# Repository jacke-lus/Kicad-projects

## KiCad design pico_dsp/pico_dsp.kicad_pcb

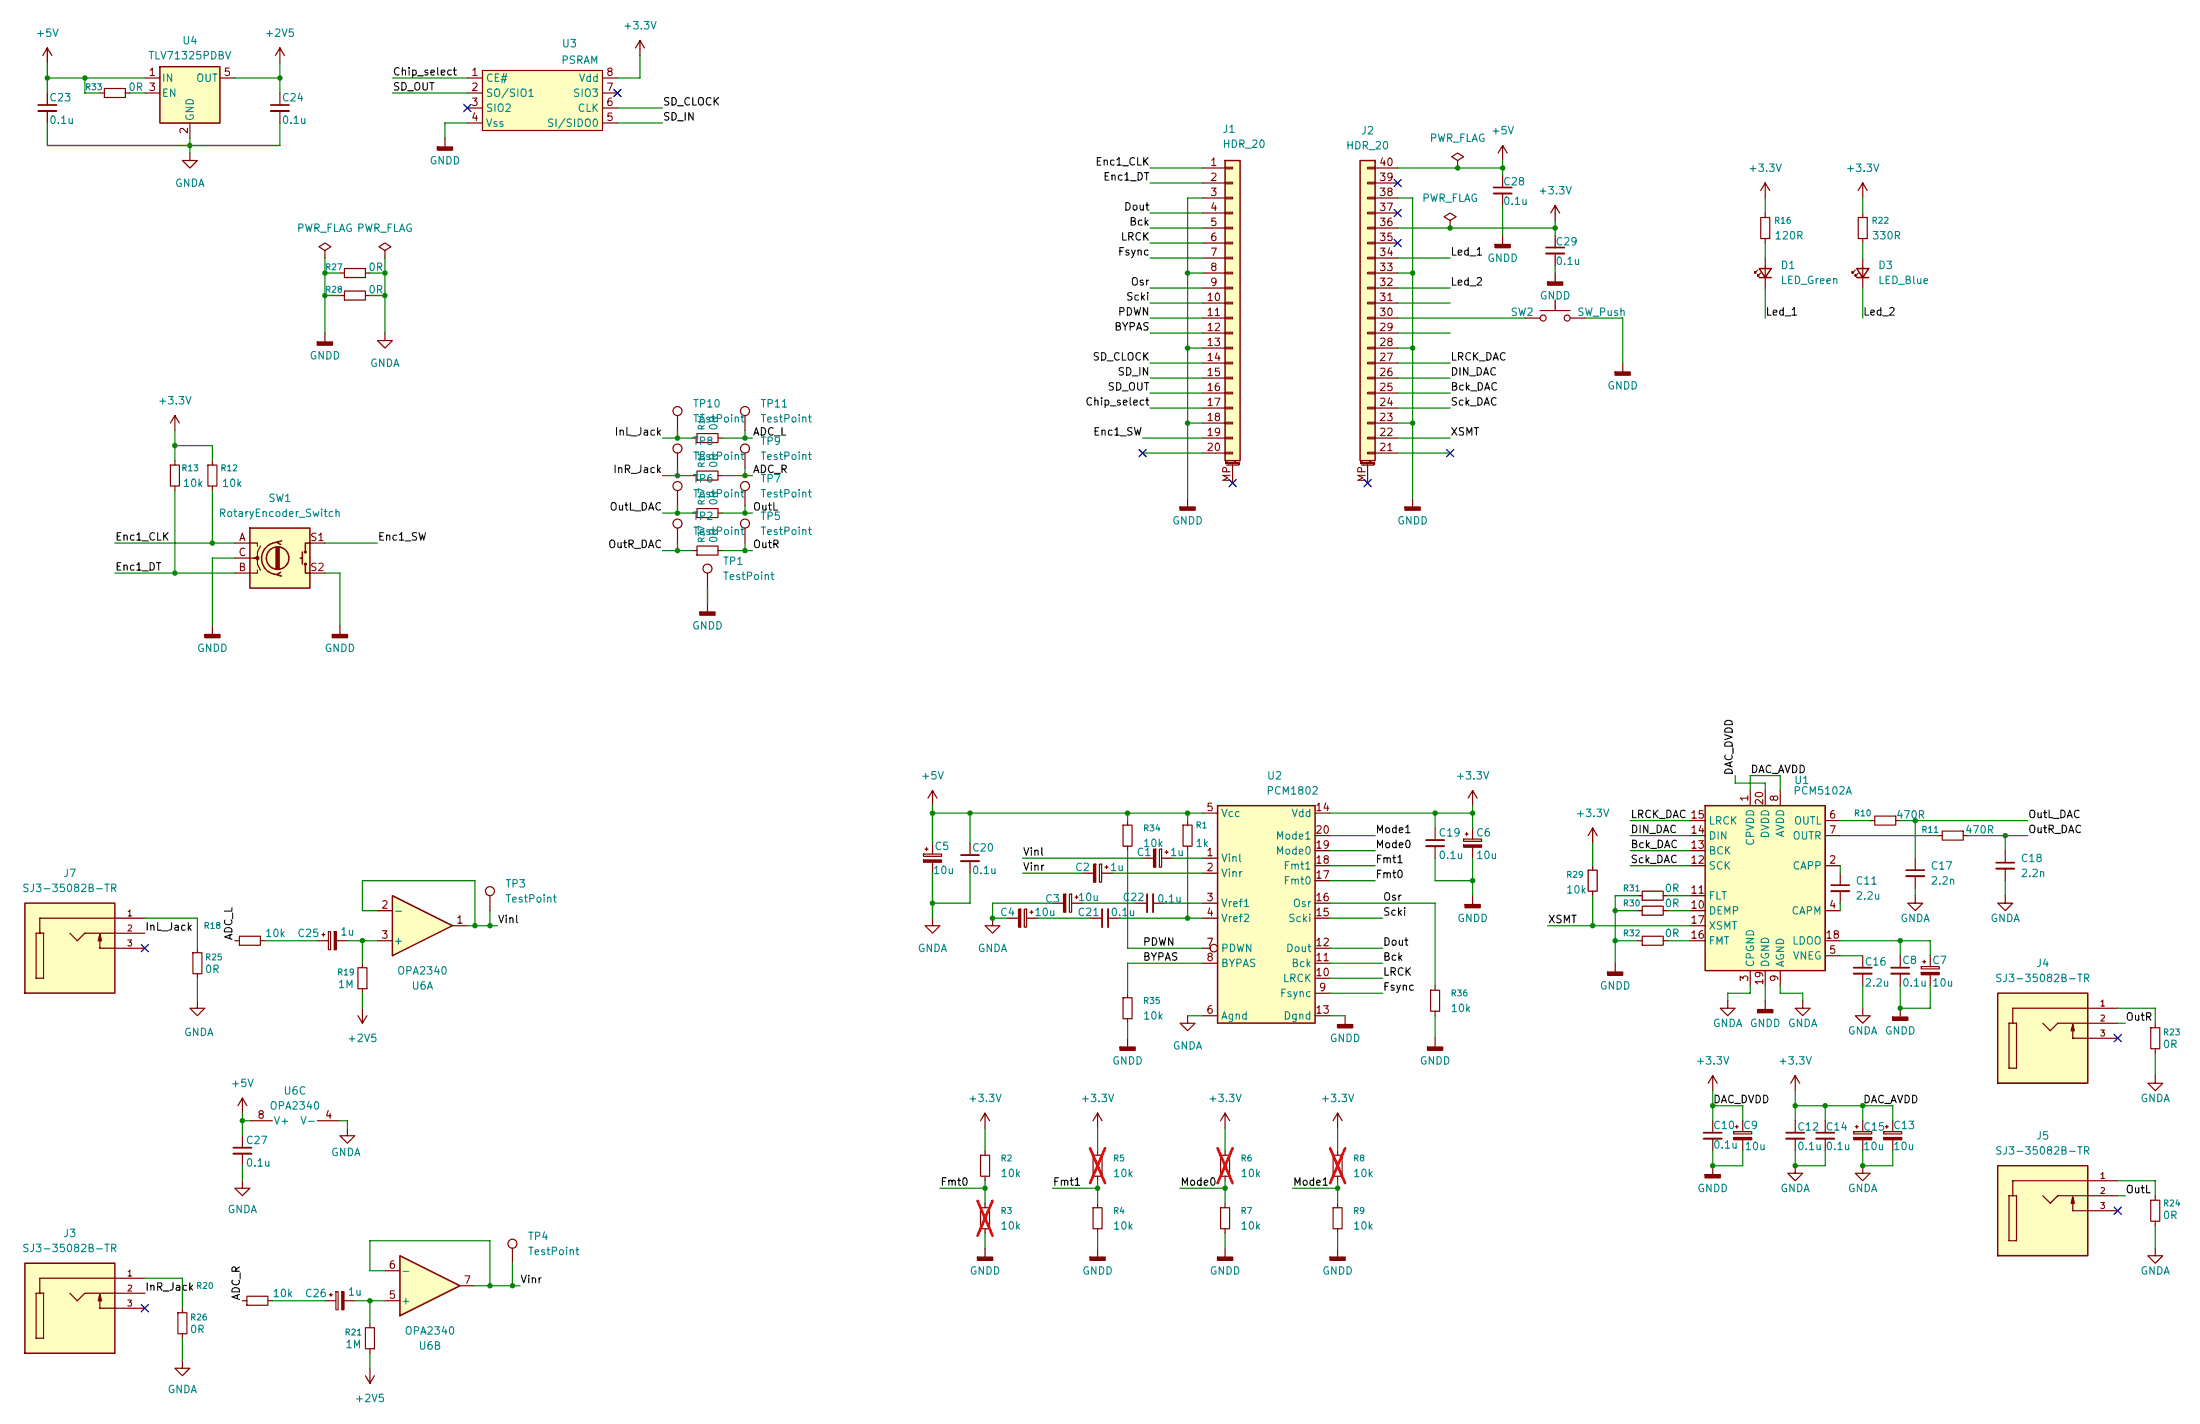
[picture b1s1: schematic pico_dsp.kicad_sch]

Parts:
C1, C2, C25, C26: 1u; CP_Elec_4x4.5
C3, C4, C5, C6, C7, C9, C13, C15: 10u; CP_Elec_4x4.5
C8, C10, C12, C14, C19, C20, C21, C22, C23, C24, C27, C28, C29: 0.1u; C_0603_1608Metric
C11, C16: 2.2u; C_0603_1608Metric
C17, C18: 2.2n; C_0603_1608Metric
D1: LED_Green; LED_0603_1608Metric
D3: LED_Blue; LED_0603_1608Metric
J1, J2: HDR_20; PinSocket_1x20_P2.54mm_Vertical
J3, J4, J5, J7: SJ3-35082B-TR; SAMESKY_SJ3-35082B-TR; PARTREV 1.01
R1: 1k; R_0603_1608Metric
R2, R4, R7, R9, R12, R13, R18, R20, R29, R34, R35, R36: 10k; R_0603_1608Metric
R3, R5, R6, R8: 10k; R_0603_1608Metric; not fitted
R10, R11: 470R; R_0603_1608Metric
R14, R15, R17, R23, R24, R25, R26, R27, R28, R30, R31, R32, R33, R37: 0R; R_0603_1608Metric
R16: 120R; R_0603_1608Metric
R19, R21: 1M; R_0603_1608Metric
R22: 330R; R_0603_1608Metric
SW1: RotaryEncoder_Switch; RotaryEncoder_Bourns_Vertical_PEC12R-3x17F-Sxxxx
SW2: SW_Push; SW_PUSH_6mm
TP1, TP2, TP3, TP4, TP5, TP6, TP7, TP8, TP9, TP10, TP11: TestPoint; TestPoint_Pad_1.5x1.5mm
U1: PCM5102A; TSSOP-20_4.4x6.5mm_P0.65mm
U2: PCM1802; SSOP-20_5.3x7.2mm_P0.65mm
U3: PSRAM; SOIC-8_3.9x4.9mm_P1.27mm
U4: TLV71325PDBV; SOT-23-5
U6: OPA2340; SOIC-8_3.9x4.9mm_P1.27mm

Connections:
+2V5: C24.1, R19.1, R21.1, U4.5 (OUT)
+3.3V: C6.1, C9.1, C10.1, C12.1, C13.1, C14.1, C15.1, C19.1, C29.1, J2.36, R2.1, R5.1, R6.1, R8.1, R12.1, R13.1, R16.2, R22.2, R29.1, U1.1 (CPVDD), U1.8 (AVDD), U1.20 (DVDD), U2.14 (Vdd), U3.8 (Vdd)
+5V: C5.1, C20.1, C23.1, C27.1, C28.1, J2.40, R1.1, R33.1, R34.1, U2.5 (Vcc), U4.1 (IN), U6.8 (V+)
/ADC_L: R14.2, R18.1, TP11.1; also elsewhere on the board
/ADC_R: R15.2, R20.1, TP9.1; also elsewhere on the board
/BYPAS: J1.12, R35.1, U2.8 (BYPAS)
/Bck: J1.5, U2.11 (Bck)
/Bck_DAC: J2.25, U1.13 (BCK)
/Chip_select: J1.17, U3.1 (CE#)
/DIN_DAC: J2.26, U1.14 (DIN)
/Dout: J1.4, U2.12 (Dout)
/Enc1_CLK: J1.1, R12.2, SW1.A
/Enc1_DT: J1.2, R13.2, SW1.B
/Enc1_SW: J1.19, SW1.S1
/Fmt0: R2.2, R3.1, U2.17 (Fmt0)
/Fmt1: R4.1, R5.2, U2.18 (Fmt1)
/Fsync: J1.7, U2.9 (Fsync)
/InL_Jack: J7.2, R14.1, TP10.1; also elsewhere on the board
/InR_Jack: J3.2, R15.1, TP8.1; also elsewhere on the board
/LRCK: J1.6, U2.10 (LRCK)
/LRCK_DAC: J2.27, U1.15 (LRCK)
/Led_1: D1.1 (K), J2.34
/Led_2: D3.1 (K), J2.32
/Mode0: R6.2, R7.1, U2.19 (Mode0)
/Mode1: R8.2, R9.1, U2.20 (Mode1)
/Osr: J1.9, R36.1, U2.16 (Osr)
/OutL: J5.2, R17.2, TP7.1; also elsewhere on the board
/OutL_DAC: C17.1, R10.1, R17.1, TP6.1; also elsewhere on the board
/OutR: J4.2, R37.2, TP5.1
/OutR_DAC: C18.1, R11.1, R37.1, TP2.1
/PDWN: J1.11, R34.2, U2.7 (PDWN)
/SD_CLOCK: J1.14, U3.6 (CLK)
/SD_IN: J1.15, U3.5 (SI/SIDO0)
/SD_OUT: J1.16, U3.2 (SO/SIO1)
/Sck_DAC: J2.24, U1.12 (SCK)
/Scki: J1.10, U2.15 (Scki)
/Vinl: C1.2, TP3.1, U6.1, U6.2 (-)
/Vinr: C2.2, TP4.1, U6.6 (-), U6.7
/XSMT: J2.22 (Pin_19), R29.2, U1.17 (XSMT)
GNDA: C3.2, C4.2, C5.2, C12.2, C13.2, C14.2, C15.2, C16.2, C17.2, C18.2, C20.2, C23.2, C24.2, C27.2, R23.2, R24.2, R25.2, R26.2, R27.2, R28.2, U1.3 (CPGND), U1.9 (AGND), U2.6 (Agnd), U4.2 (GND), U6.4 (V-)
GNDD: C6.2, C7.2, C8.2, C9.2, C10.2, C19.2, C28.2, C29.2, J1.3, J1.8, J1.13, J1.18, J2.23 (Pin_18), J2.28, J2.33, J2.38, R3.2, R4.2, R7.2, R9.2, R27.1, R28.1, R30.1, R31.1, R32.1, R35.2, R36.2, SW1.C, SW1.S2, SW2.2, TP1.1, U1.19 (DGND), U2.13 (Dgnd), U3.4 (Vss)
unnamed: C4.1, C21.1
unnamed: C3.1, C22.1
unnamed: C25.1, R18.2
unnamed: C26.1, R20.2
unnamed: D1.2 (A), R16.1
unnamed: D3.2 (A), R22.1
unnamed: J2.30, SW2.1
unnamed: J3.1, R26.1
unnamed: J4.1, R23.1
unnamed: J5.1, R24.1
unnamed: J7.1, R25.1
unnamed: C11.2, U1.4 (CAPM)
unnamed: C11.1, U1.2 (CAPP)
unnamed: R30.2, U1.10 (DEMP)
unnamed: R31.2, U1.11 (FLT)
unnamed: R32.2, U1.16 (FMT)
unnamed: C7.1, C8.1, U1.18 (LDOO)
unnamed: R10.2, U1.6 (OUTL)
unnamed: R11.2, U1.7 (OUTR)
unnamed: C16.1, U1.5 (VNEG)
unnamed: C1.1, U2.1 (Vinl)
unnamed: C2.1, U2.2 (Vinr)
unnamed: C22.2, U2.3 (Vref1)
unnamed: C21.2, R1.2, U2.4 (Vref2)
unnamed: R33.2, U4.3 (EN)
unnamed: C25.2, R19.2, U6.3 (+)
unnamed: C26.2, R21.2, U6.5 (+)

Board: 2 copper layers, 95 parts (38 on the bottom side), 68 nets, no tracks yet.

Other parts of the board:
R14#2, R15#2, R17#2: 0R; R_0603_1608Metric

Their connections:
/ADC_L: R14#2.2; also elsewhere on the board
/ADC_R: R15#2.2; also elsewhere on the board
/InL_Jack: R14#2.1; also elsewhere on the board
/InR_Jack: R15#2.1; also elsewhere on the board
/OutL: R17#2.2; also elsewhere on the board
/OutL_DAC: R17#2.1; also elsewhere on the board

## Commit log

2025-07-04 initial push
2025-07-16 Added pads and updated pcb
